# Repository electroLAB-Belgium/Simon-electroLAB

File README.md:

# Simon electroLAB
 This little PCB (created with Kicad 8) is a simple Simon game. The goal is to teach children electronics soldering using TH components

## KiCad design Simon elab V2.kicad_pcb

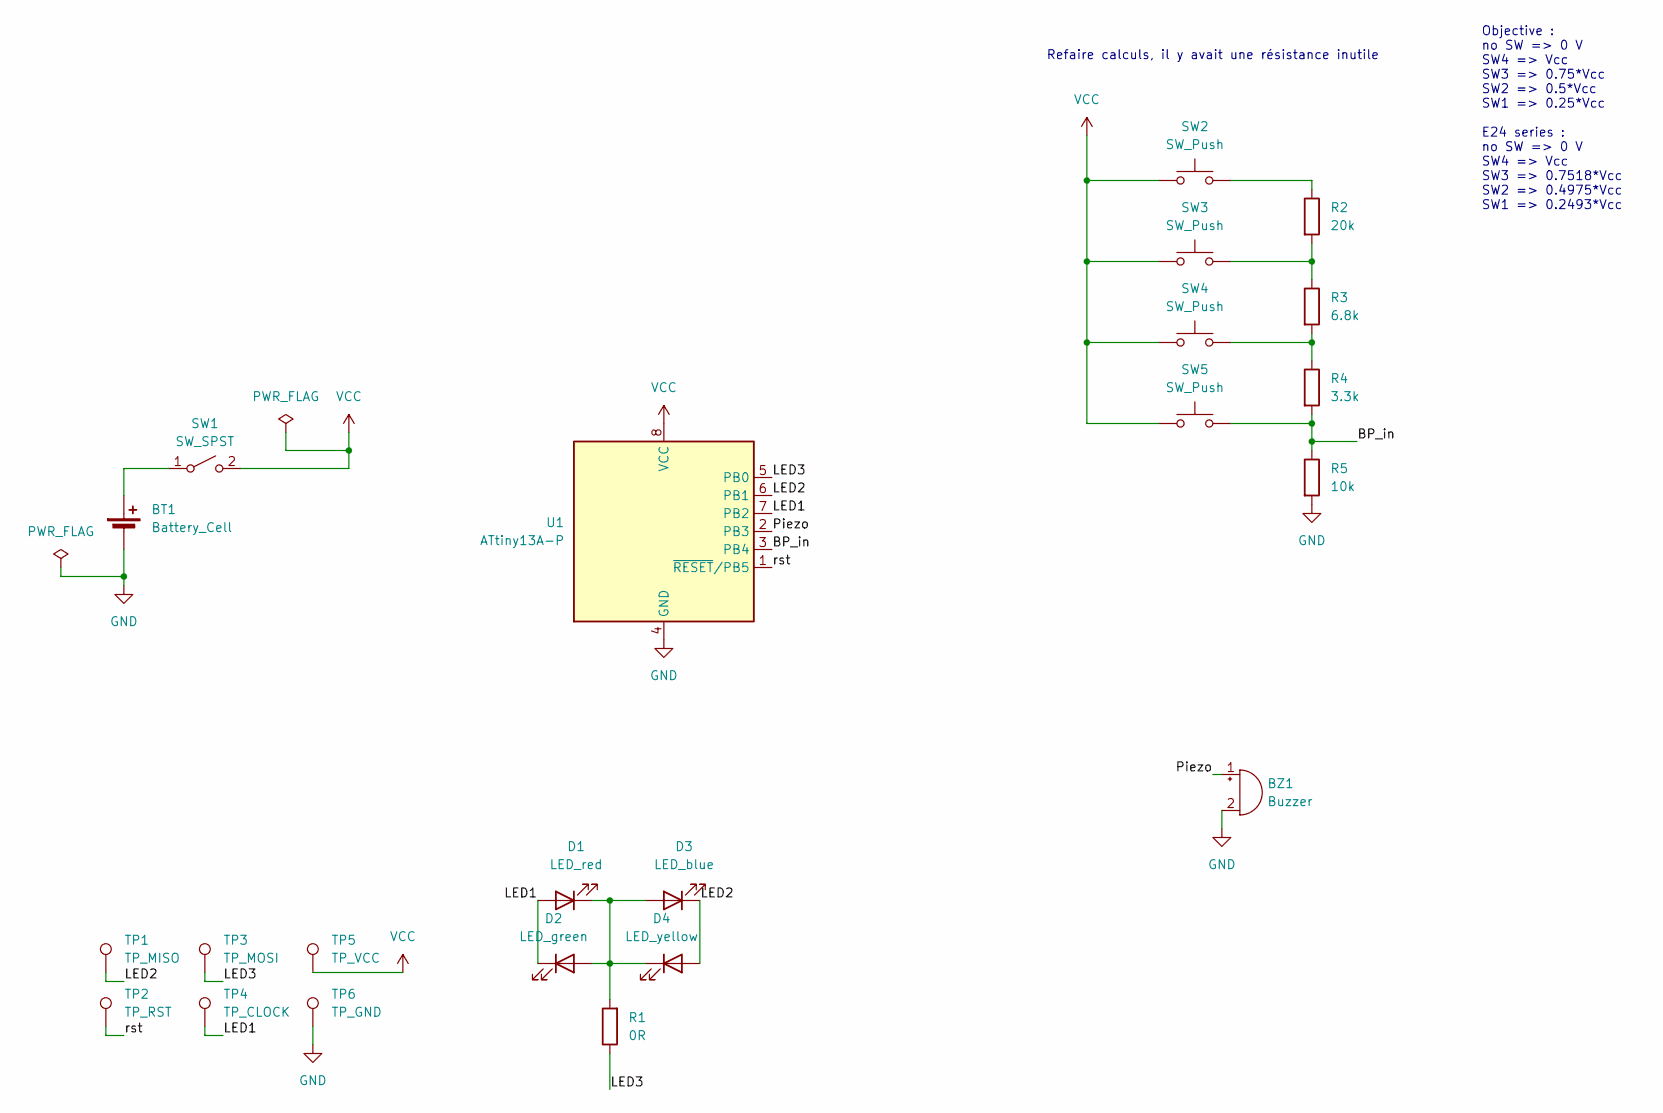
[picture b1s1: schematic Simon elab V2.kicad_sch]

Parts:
BT1: Battery_Cell; BatteryHolder_Keystone_103_1x20mm
BZ1: Buzzer; Buzzer_TDK_PS1240P02BT_D12.2mm_H6.5mm
D1: LED_red; LED_D5.0mm
D2: LED_green; LED_D5.0mm
D3: LED_blue; LED_D5.0mm
D4: LED_yellow; LED_D5.0mm
R1: 0R; R_Axial_DIN0207_L6.3mm_D2.5mm_P7.62mm_Horizontal
R2: 20k; R_Axial_DIN0207_L6.3mm_D2.5mm_P7.62mm_Horizontal
R3: 6.8k; R_Axial_DIN0207_L6.3mm_D2.5mm_P7.62mm_Horizontal
R4: 3.3k; R_Axial_DIN0207_L6.3mm_D2.5mm_P7.62mm_Horizontal
R5: 10k; R_Axial_DIN0207_L6.3mm_D2.5mm_P7.62mm_Horizontal
SW1: SW_SPST; SW_Slide_SPDT_Angled_CK_OS102011MA1Q
SW2, SW3, SW4, SW5: SW_Push; SW_PUSH_6mm_H5mm
TP1: TP_MISO; TestPoint_Pad_D2.5mm
TP2: TP_RST; TestPoint_Pad_D2.5mm
TP3: TP_MOSI; TestPoint_Pad_D2.5mm
TP4: TP_CLOCK; TestPoint_Pad_D2.5mm
TP5: TP_VCC; TestPoint_Pad_D2.5mm
TP6: TP_GND; TestPoint_Pad_D2.5mm
U1: ATtiny13A-P; DIP-8_W7.62mm

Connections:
/BP_in: R4.2, R5.1, SW5.2, U1.3 (PB4)
/LED1: D1.2 (A), D2.1 (K), TP4.1, U1.7 (PB2)
/LED2: D3.1 (K), D4.2 (A), TP1.1, U1.6 (PB1)
/LED3: R1.1, TP3.1, U1.5 (PB0)
/Piezo: BZ1.1 (+), U1.2 (PB3)
/rst: TP2.1, U1.1 (~RESET/PB5)
GND: BT1.2 (-), BZ1.2 (-), R5.2, TP6.1, U1.4 (GND)
unnamed: BT1.1 (+), SW1.1 (A)
unnamed: D1.1 (K), D2.2 (A), D3.2 (A), D4.1 (K), R1.2
unnamed: R2.1, SW2.2
unnamed: R2.2, R3.1, SW3.2
unnamed: R3.2, R4.1, SW4.2
VCC: SW1.2 (B), SW2.1, SW3.1, SW4.1, SW5.1, TP5.1, U1.8 (VCC)

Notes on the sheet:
Objective : no SW => 0 V SW4 => Vcc SW3 => 0.75*Vcc SW2 => 0.5*Vcc SW1 => 0.25*Vcc E24 series : no SW => 0 V SW4 => Vcc SW3 => 0.7518*Vcc SW2 => 0.4975*Vcc SW1 => 0.2493*Vcc
Refaire calculs, il y avait une résistance inutile

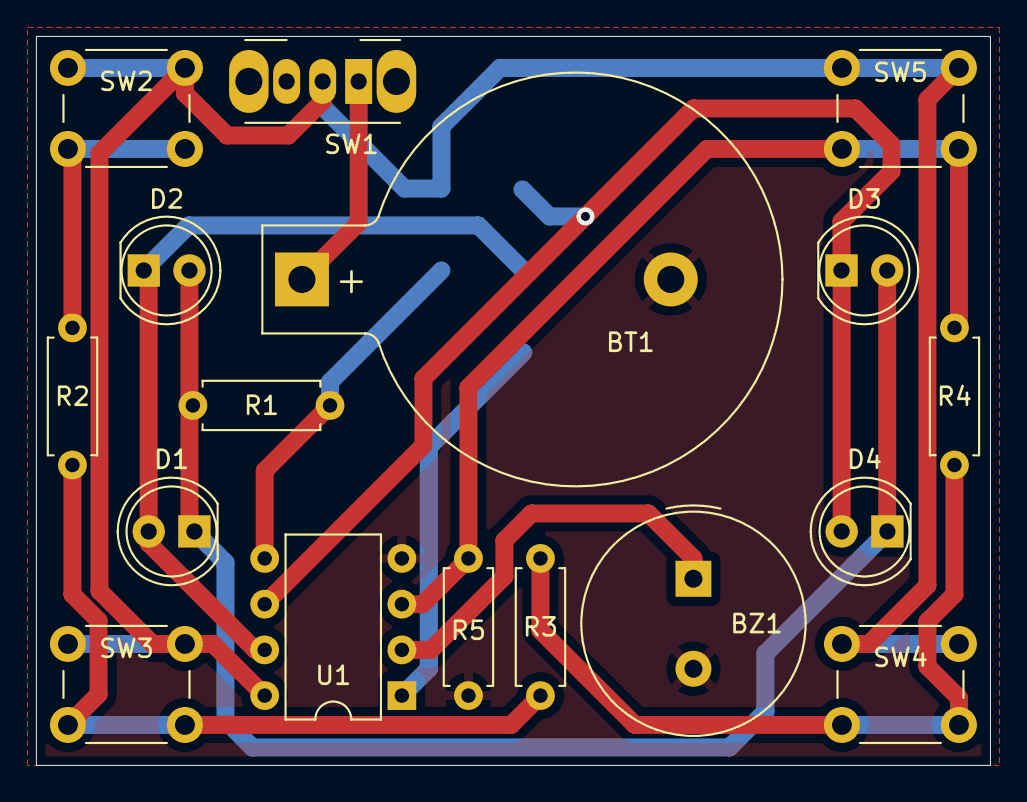
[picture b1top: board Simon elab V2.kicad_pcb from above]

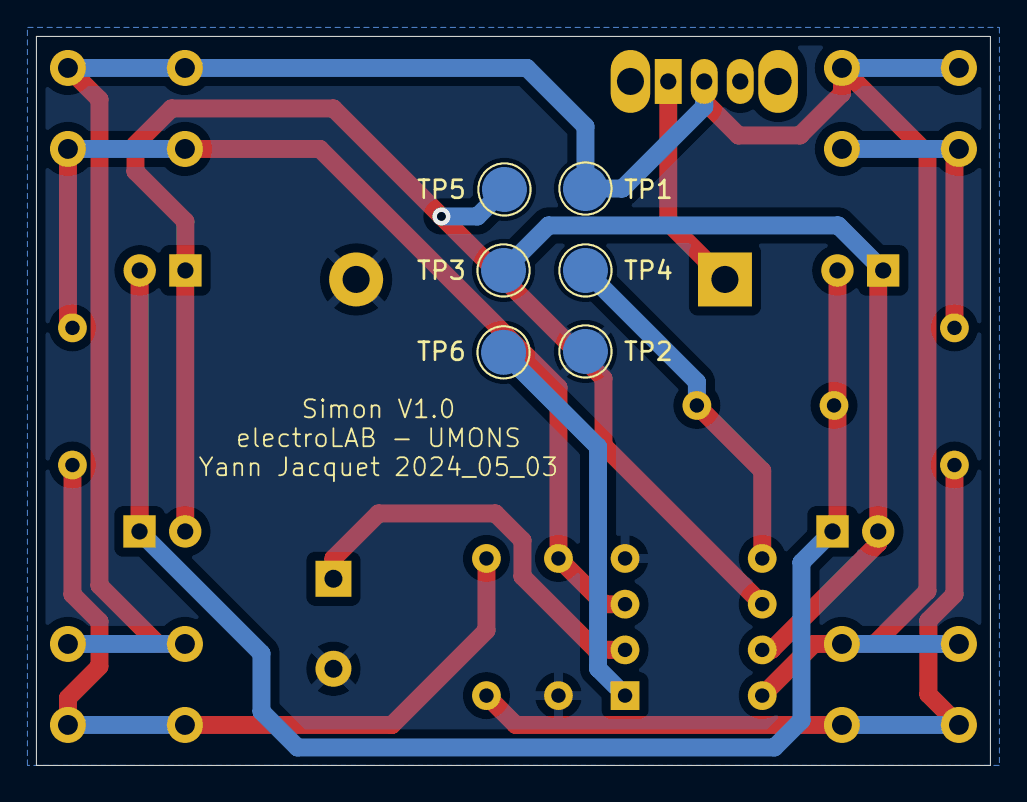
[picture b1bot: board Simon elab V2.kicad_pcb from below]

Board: 2 copper layers, 53.0 x 40.5 mm, 23 parts (6 on the bottom side), 13 nets.

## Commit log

2024-05-03 Silk screen and edge cuts edit
    Silk screen
    Edge cuts
    Adding DNG filled zone F.Cu
    Correcting TP at bottom layer
2024-05-03 V1.0 Gerber creation
